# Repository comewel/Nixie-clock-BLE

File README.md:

# Nixie-clock-BLE
Project inspired by [GreatScott!](https://www.youtube.com/watch?v=ObgmVNV1Kfg)'s video. The main difference is in the MCU choice, in this project it is used the ESP32 to give the Nixie clock the change of time capabilities with bluetooth.

## PCB looks like
#### Front:

#### Back:

## List of components

The raw list
- 1 x ESP32 
- 4 x Nixie clock tube (IN-14 type)
- 4 x Nixie clock driver
- 1 x RTC (In the project it was used the DS 3231 shield)
- 1 x Boost converter (in order to get the 170V required by the nixie tubes)
- 1 x Voltage regulator (In the project it was used an L7805CV)
- 2 x 10uF capacitors (for the 12V and 5V lines)
- 4 x 100nF capacitors (one for each nixie driver)
- 4 x 10K Resistors (one between each nixie clock's anode and 170V)
Should be it.

## The firmware
The only piece that is required to fill is the `NIXIE_CLOCK_SERVICE_UUID` definition.

## 3D printing design files
Inside the folder `3D-case-design` there are the AutoDesk Fusion 360 design files used for this project in `.stl` and `.f3d` format.
Click [here](./3D-case-design/case.stl) for a preview of the case design.

:exclamation:  Please notice that the lid is slightly off. We have made only a simple draft and then decided to leave it as it was (see notes below).

## Notes
1. In the current project the majority of components are in the same side of the Nixie tubes. This will prevent the use of a top flat cover, unless you decide to put a lot of holes in it.
So all the components should be moved on the back side and rearranging the connection in accordance.
2. The nixie clock tubes used for the hour and the one used for the minutes are not symmetrical to the center of the PCB.

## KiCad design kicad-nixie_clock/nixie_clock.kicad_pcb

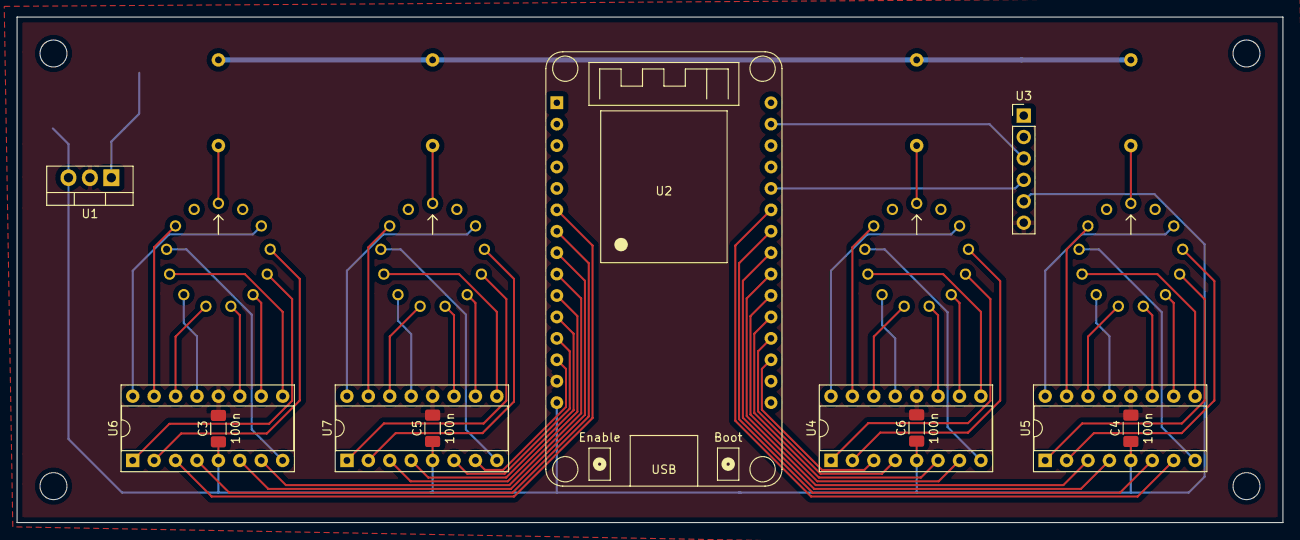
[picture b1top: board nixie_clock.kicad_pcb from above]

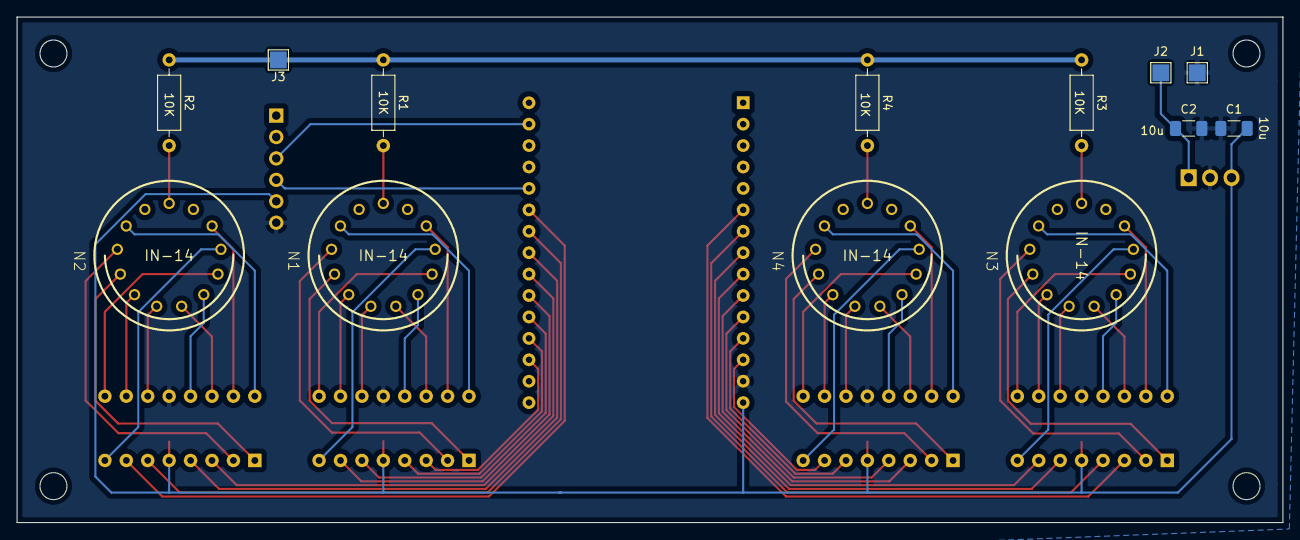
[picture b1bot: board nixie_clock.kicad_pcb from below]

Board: 2 copper layers, 150.1 x 59.9 mm, 24 parts (13 on the bottom side), 66 nets.

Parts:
C1, C2: 10u; C_1206_3216Metric_Pad1.33x1.80mm_HandSolder
C3, C4, C5, C6: 100n; C_1206_3216Metric_Pad1.33x1.80mm_HandSolder
J1: GND; TestPoint_Pad_2.0x2.0mm
J2: 12V; TestPoint_Pad_2.0x2.0mm
J3: 170V; TestPoint_Pad_2.0x2.0mm
N1, N2, N3, N4: IN-14; nixies-us-IN-14
R1, R2, R3, R4: 10K; R_Axial_DIN0207_L6.3mm_D2.5mm_P10.16mm_Horizontal
U1: LM7805_TO220; TO-220-3_Vertical
U2: ESP32_DevKit_V1_DOIT; footprints_esp32_devkit_v1_doit.pretty_esp32_devkit_v1_doit
U3: RTC-devkit; PinHeader_1x06_P2.54mm_Vertical
U4, U5, U6, U7: K155ID1; DIP-16_W7.62mm_Socket

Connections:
+5V: C1.1, C3.1, C4.1, C5.1, C6.1, U1.3, U2.15, U3.5, U4.5, U5.5, U6.5, U7.5
+12V: C2.1, J2.1, U1.1
/+170: J3.1, R1.1, R2.1, R3.1, R4.1
/A1: U2.18, U4.3
/A2: U2.22, U5.3
/A3: U2.6, U6.3
/A4: U2.10, U7.3
/B1: U2.20, U4.6
/B2: U2.24, U5.6
/B3: U2.8, U6.6
/B4: U2.12, U7.6
/C1: U2.21, U4.7
/C2: U2.25, U5.7
/C3: U2.9, U6.7
/C4: U2.13, U7.7
/D1: U2.19, U4.4
/D2: U2.23, U5.4
/D3: U2.7, U6.4
/D4: U2.11, U7.4
GND: C1.2, C2.2, C3.2, C4.2, C5.2, C6.2, J1.1, U1.2, U2.14, U3.6, U4.12, U5.12, U6.12, U7.12
unnamed: N1.0, U4.16
unnamed: N1.1, U4.15
unnamed: N1.2, U4.8
unnamed: N1.3, U4.9
unnamed: N1.4, U4.13
unnamed: N1.5, U4.14
unnamed: N1.6, U4.11
unnamed: N1.7, U4.10
unnamed: N1.8, U4.1
unnamed: N1.9, U4.2
unnamed: N1.A, R1.2
unnamed: N2.0, U5.16
unnamed: N2.1, U5.15
unnamed: N2.2, U5.8
unnamed: N2.3, U5.9
unnamed: N2.4, U5.13
unnamed: N2.5, U5.14
unnamed: N2.6, U5.11
unnamed: N2.7, U5.10
unnamed: N2.8, U5.1
unnamed: N2.9, U5.2
unnamed: N2.A, R2.2
unnamed: N3.0, U6.16
unnamed: N3.1, U6.15
unnamed: N3.2, U6.8
unnamed: N3.3, U6.9
unnamed: N3.4, U6.13
unnamed: N3.5, U6.14
unnamed: N3.6, U6.11
unnamed: N3.7, U6.10
unnamed: N3.8, U6.1
unnamed: N3.9, U6.2
unnamed: N3.A, R3.2
unnamed: N4.0, U7.16
unnamed: N4.1, U7.15
unnamed: N4.2, U7.8
unnamed: N4.3, U7.9
unnamed: N4.4, U7.13
unnamed: N4.5, U7.14
unnamed: N4.6, U7.11
unnamed: N4.7, U7.10
unnamed: N4.8, U7.1
unnamed: N4.9, U7.2
unnamed: N4.A, R4.2
unnamed: U2.26, U3.4
unnamed: U2.29, U3.3

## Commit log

2021-02-12 add gitignore
2021-02-12 add esp32 firmware
2021-02-12 add kicad project
2021-02-12 add README with images
2021-02-12 fix readme
2021-02-13 3D printing design files added
2021-02-15 fix project name
